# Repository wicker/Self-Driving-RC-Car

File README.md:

Self-Driving-RC-Car
===================

Testing out Kalman filter and SLAM code on a vehicle which can't fall out of the sky.

Hardware
--------

IMX (Imex) Firefox 1/10 scale RC car contains one RC550 brushed hobby DC motor and one three-wire RadioShack hobby servo. 

v1 controller is an Arduino Uno with VNH5019 Dual Motor Driver Carrier Shield from Pololu. 

v2 controller is an STM32F4-Discovery board with VNH5019 Dual Motor Driver Carrier shield from Pololu.

v3 controller is a custom Foxcar Control Board v1.

v4 controller is a custom Foxcar Control Board v2.

Software
--------

**v1 - Arduino**

A simple Arduino sketch to drive the motor in forward and reverse while turning the servo to steer the vehicle. Libraries used:

- [Zambetti's ASCIITable](http://arduino.cc/en/Tutorial/ASCIITable)
- [SoftwareSerial](http://arduino.cc/en/Reference/SoftwareSerial)
- [mem's ServoTimer2](http://forum.arduino.cc/index.php/topic,21975.0.html)
- [Pololu's VNH5019 Motor Driver Shield](https://github.com/pololu/dual-vnh5019-motor-shield)

**v2 - STM32F4-Discovery**

Putting everything together. 

- [Pololu's VNH5019 Motor Driver Shield](https://github.com/pololu/dual-vnh5019-motor-shield)

License
-------

Released under the 3-clause BSD. http://opensource.org/licenses/BSD-3-Clause

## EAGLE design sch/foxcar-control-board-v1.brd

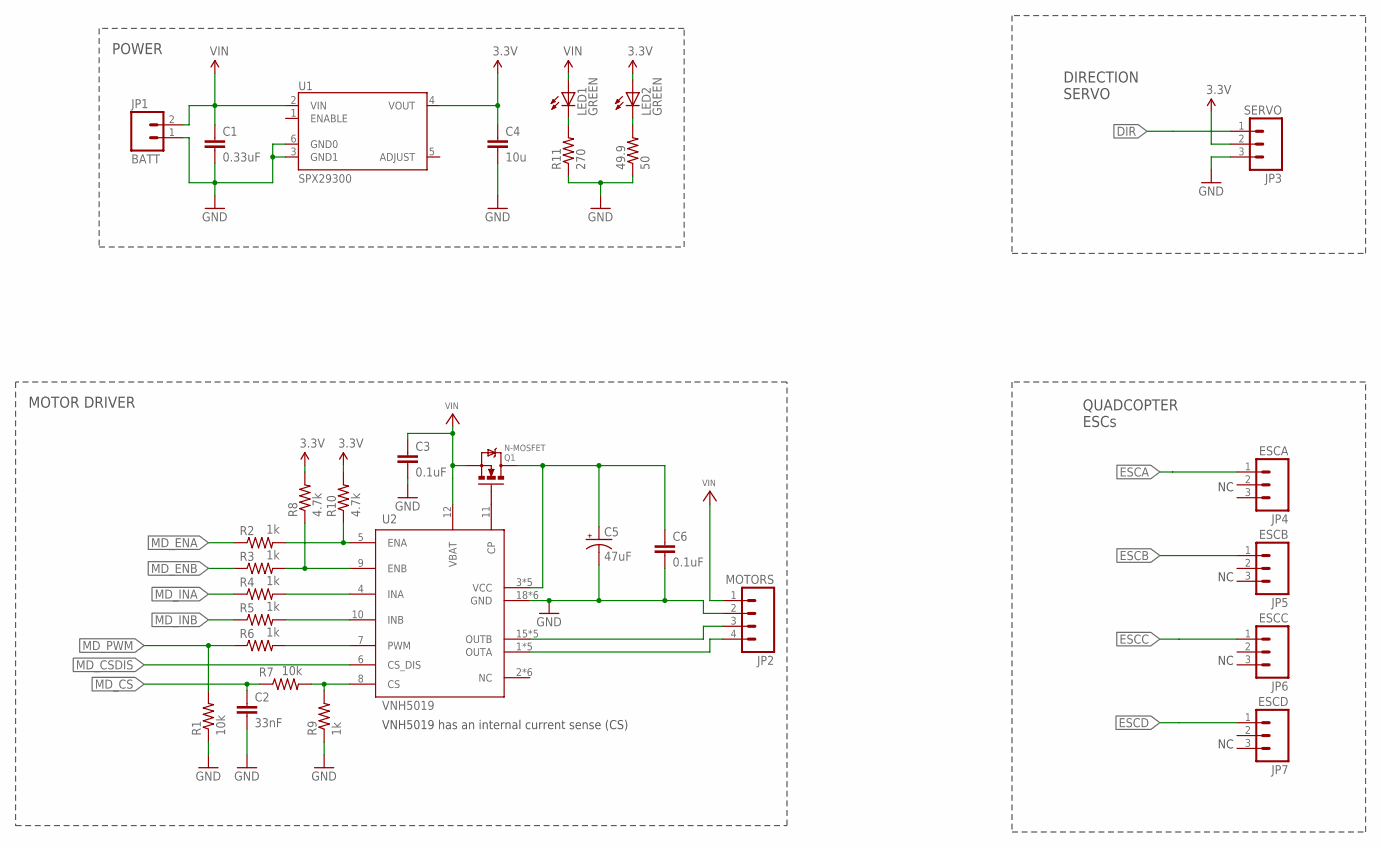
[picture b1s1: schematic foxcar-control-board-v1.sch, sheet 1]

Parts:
49.9: 50; 0402-RES
C1: 0.33uF; 0402-CAP
C2: 33nF; 0402-CAP
C3, C6: 0.1uF; 0402-CAP
C4: 10u; 0603-CAP
C5: 47uF; PANASONIC_D
JP1: BATT; SCREWTERMINAL-3.5MM-2_LOCK
JP2: MOTORS; SCREWTERMINAL-3.5MM-4_LOCK
JP3: SERVO; 1X03_LOCK_LONGPADS
JP4: ESCA; 1X03_LOCK_LONGPADS
JP5: ESCB; 1X03_LOCK_LONGPADS
JP6: ESCC; 1X03_LOCK_LONGPADS
JP7: ESCD; 1X03_LOCK_LONGPADS
LED1, LED2: GREEN; CHIPLED_0603
Q1: N-MOSFET; TO220V
R1: 10k; 0603-RES
R2, R3, R4, R5, R6, R9: 1k; 0402-RES
R7: 10k; 0402-RES
R8, R10: 4.7k; 0402-RES
R11: 270; 0603-RES
U1: SPX29300; TO263-5
U2: VNH5019; MULTIPOWERSO-30

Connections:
3.3V: C4.1, JP3.2, LED2.A, R8.2, R10.2, U1.4 (VOUT); also elsewhere on the board
CP: Q1.1 (G), U2.11 (CP)
CS: R7.2, R9.2, U2.8 (CS)
DIR: JP3.1; also elsewhere on the board
ENA: R2.2, R10.1, U2.5 (ENA)
ENB: R3.2, R8.1, U2.9 (ENB)
ESCA: JP4.1; also elsewhere on the board
ESCB: JP5.1; also elsewhere on the board
ESCC: JP6.1; also elsewhere on the board
ESCD: JP7.1; also elsewhere on the board
GND: 49.9.1, C1.2, C2.2, C3.2, C4.2, C5.-, C6.2, JP1.1, JP2.2, JP3.3, R1.1, R9.1, R11.1, U1.3 (GND1), U1.6 (GND0), U2.18 (GND), U2.19 (GND), U2.20 (GND), U2.26 (GND), U2.27 (GND), U2.28 (GND); also elsewhere on the board
INA: R4.2, U2.4 (INA)
INB: R5.2, U2.10 (INB)
MD_CS: C2.1, R7.1; also elsewhere on the board
MD_CSDIS: U2.6 (CS_DIS); also elsewhere on the board
MD_ENA: R2.1; also elsewhere on the board
MD_ENB: R3.1; also elsewhere on the board
MD_INA: R4.1; also elsewhere on the board
MD_INB: R5.1; also elsewhere on the board
MD_PWM: R1.2, R6.1; also elsewhere on the board
unnamed: 49.9.2, LED2.C
unnamed: LED1.C, R11.2
OUTA: JP2.4, U2.1 (OUTA), U2.25 (OUTA), U2.30 (OUTA), U2.OUTA, U2.OUTA@1 (OUTA)
OUTB: JP2.3, U2.15 (OUTB), U2.16 (OUTB), U2.21 (OUTB), U2.OUTB, U2.OUTB@1 (OUTB)
PWM: R6.2, U2.7 (PWM)
VCC: C5.+, C6.1, Q1.2 (D), U2.3 (VCC), U2.13 (VCC), U2.23 (VCC), U2.VCC, U2.VCC@1 (VCC)
VIN: C1.1, C3.1, JP1.2, JP2.1, LED1.A, Q1.3 (S), U1.2 (VIN), U2.12 (VBAT); also elsewhere on the board

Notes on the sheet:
VNH5019 has an internal current sense (CS)
POWER
MOTOR DRIVER
DIRECTION SERVO
QUADCOPTER ESCs

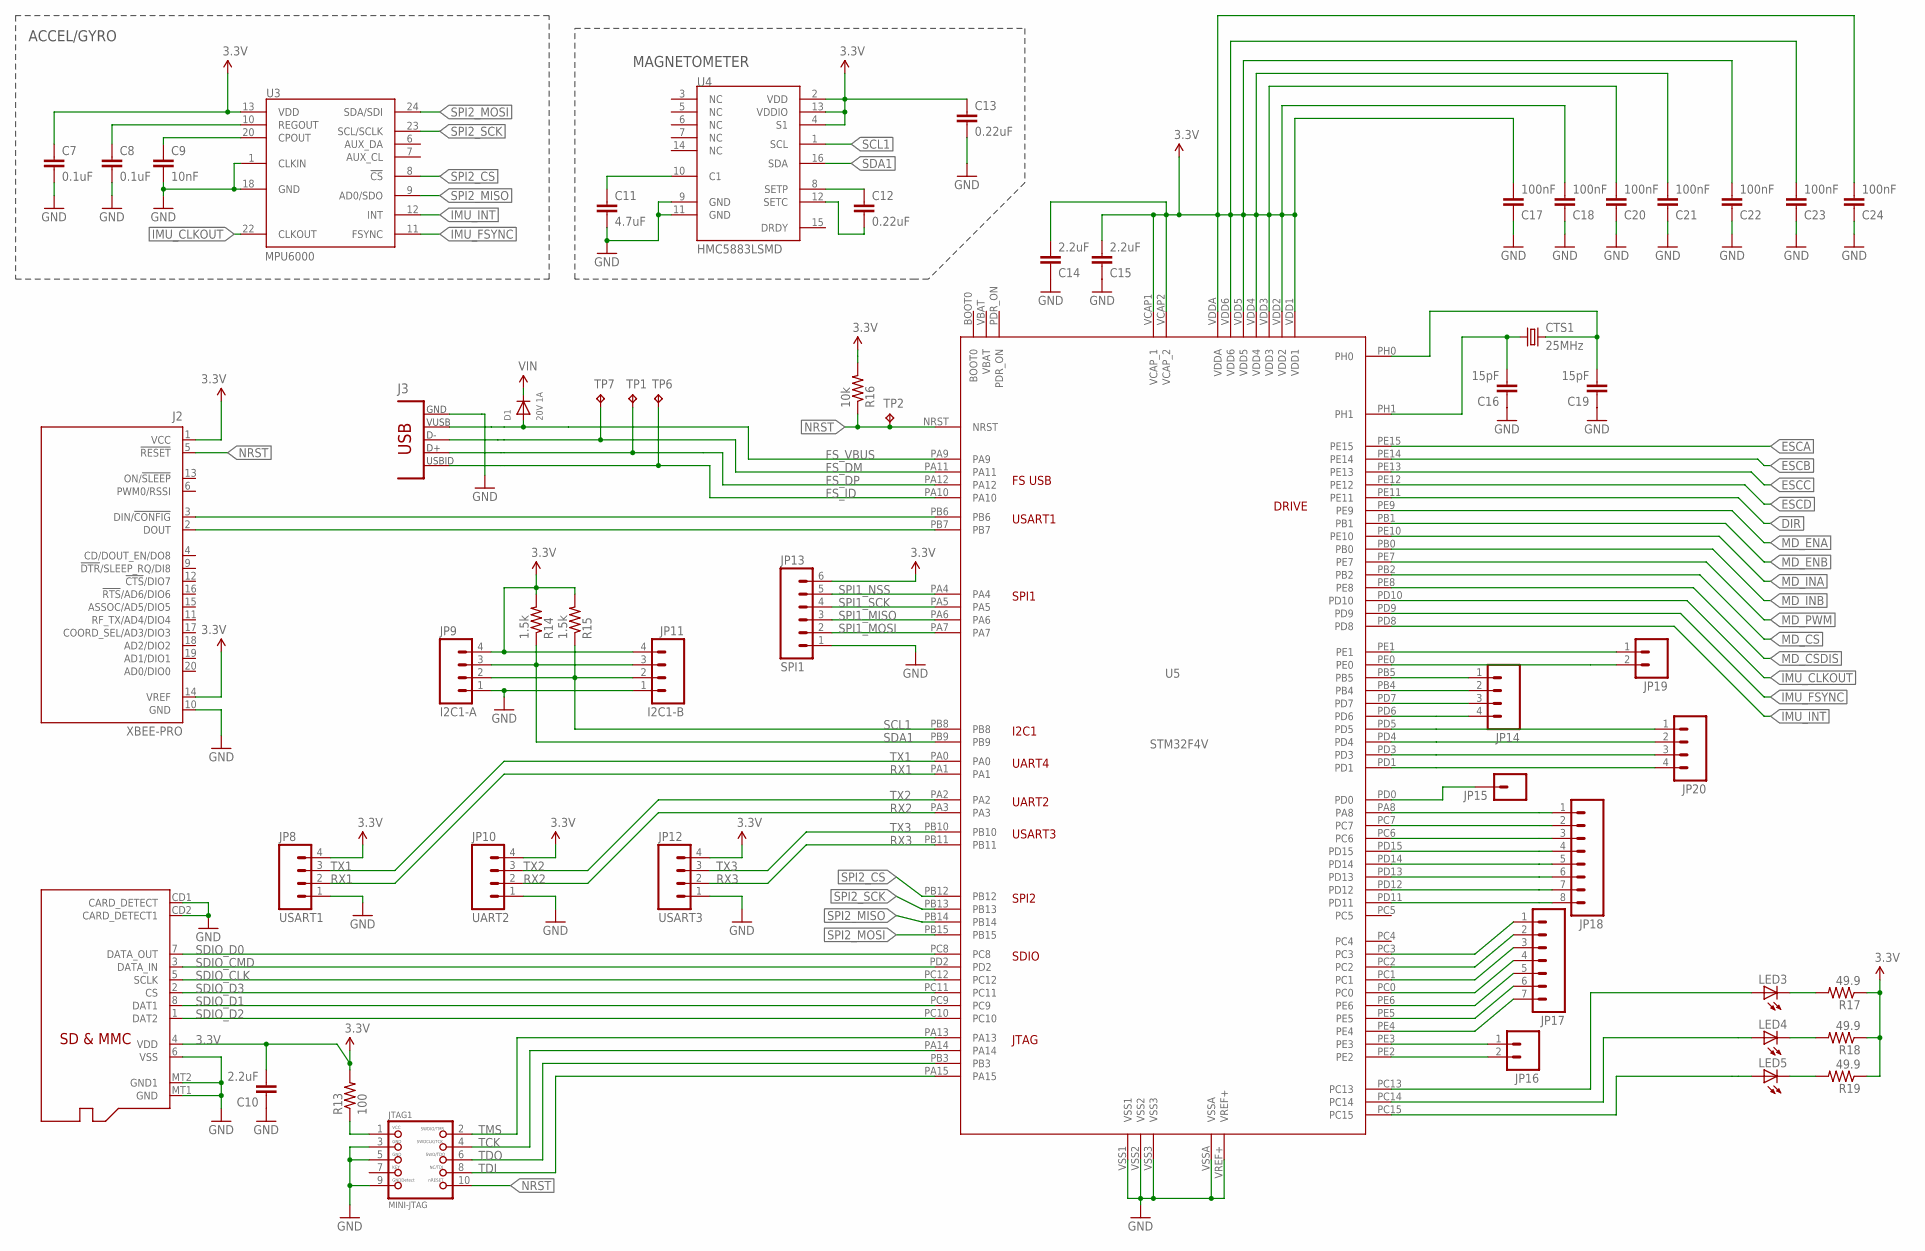
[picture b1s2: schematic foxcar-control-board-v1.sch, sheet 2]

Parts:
C7, C8: 0.1uF; 0402-CAP
C9: 10nF; 0402-CAP
C10, C14, C15: 2.2uF; 0402-CAP
C11: 4.7uF; 0402-CAP
C12, C13: 0.22uF; 0402-CAP
C16, C19: 15pF; 0402-CAP
C17, C18, C20, C21, C22, C23, C24: 100nF; 0402-CAP
CTS1: 25MHz; CTS406
D1: 20V 1A; SMADIODE
J1: MICROSD
J2: XBEE-PRO
J3: CON-USB-F-MICRO-B; CONN_USB_MICRO-B
JP8: USART1; 1X04_LOCK_LONGPADS
JP9: I2C1-A; 1X04_LOCK_LONGPADS
JP10: UART2; 1X04_LOCK_LONGPADS
JP11: I2C1-B; 1X04_LOCK_LONGPADS
JP12: USART3; 1X04_LOCK_LONGPADS
JP13: SPI1; 1X06_LOCK_LONGPADS
JP14, JP20: M04LOCK; 1X04_LOCK
JP15: M01PTH; 1X01
JP16: M02LOCK_LONGPADS; 1X02_LOCK_LONGPADS
JP17: M07LOCK; 1X07_LOCK
JP18: M08LOCK_LONGPADS; 1X08_LOCK_LONGPADS
JP19: M02LOCK; 1X02_LOCK
JTAG1: MINI-JTAG; 2X05_1.27MM_SMT
LED3, LED4, LED5: LEDCHIPLED_0603; CHIPLED_0603
R13: 100; 0402-RES
R14, R15: 1.5k; 0402-RES
R16: 10k; 0402-RES
R17, R18, R19: 49.9; 0402-RES
TP1, TP2, TP6, TP7: TPTP06R; TP06R
U3: MPU6000; QFN.24.4X4
U4: HMC5883LSMD; 16LPCC
U5: STM32F4V; LQFP100

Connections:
3.3V: C7.1, C10.2, C13.1, C14.2, C15.2, C17.2, C18.2, C20.2, C21.2, C22.2, C23.2, C24.2, J1.4 (VDD), J2.1 (VCC), J2.14 (VREF), JP8.4, JP9.4, JP10.4, JP11.4, JP12.4, JP13.6, R13.2, R14.2, R15.2, R16.2, R17.1, R18.1, R19.1, U3.13 (VDD), U4.2 (VDD), U4.4 (S1), U4.13 (VDDIO), U5.VCAP1 (VCAP_1), U5.VCAP2 (VCAP_2), U5.VDD1, U5.VDD2, U5.VDD3, U5.VDD4, U5.VDD5, U5.VDD6, U5.VDDA; also elsewhere on the board
DIR: U5.PE11; also elsewhere on the board
ESCA: U5.PE15; also elsewhere on the board
ESCB: U5.PE14; also elsewhere on the board
ESCC: U5.PE13; also elsewhere on the board
ESCD: U5.PE12; also elsewhere on the board
FS_DM: J3.P2 (D-), TP7.TP, U5.PA11
FS_DP: J3.P3 (D+), TP1.TP, U5.PA12
FS_ID: J3.P4 (USBID), TP6.TP, U5.PA10
FS_VBUS: D1.A, J3.P1 (VUSB), U5.PA9
GND: C7.2, C8.2, C9.2, C10.1, C11.2, C13.2, C14.1, C15.1, C16.1, C17.1, C18.1, C19.1, C20.1, C21.1, C22.1, C23.1, C24.1, J1.6 (VSS), J1.CD1 (CARD_DETECT), J1.CD2 (CARD_DETECT1), J1.MT1 (GND), J1.MT2 (GND1), J2.10 (GND), J3.P5 (GND), JP8.1, JP9.1, JP10.1, JP11.1, JP12.1, JP13.1, JTAG1.3, JTAG1.5, JTAG1.9, U3.1 (CLKIN), U3.18 (GND), U4.9 (GND), U4.11 (GND), U5.VREF+, U5.VSS1, U5.VSS2, U5.VSS3, U5.VSSA; also elsewhere on the board
IMU_CLKOUT: U3.22 (CLKOUT), U5.PD10
IMU_FSYNC: U3.11 (FSYNC), U5.PD9
IMU_INT: U3.12 (INT), U5.PD8
LED_B: LED5.A, U5.PC15
LED_G: LED4.A, U5.PC14
LED_R: LED3.A, U5.PC13
MD_CS: U5.PB2; also elsewhere on the board
MD_CSDIS: U5.PE8; also elsewhere on the board
MD_ENA: U5.PE9; also elsewhere on the board
MD_ENB: U5.PB1; also elsewhere on the board
MD_INA: U5.PE10; also elsewhere on the board
MD_INB: U5.PB0; also elsewhere on the board
MD_PWM: U5.PE7; also elsewhere on the board
unnamed: JP18.1, U5.PA8
unnamed: C12.2, U4.12 (SETC)
unnamed: LED3.C, R17.2
unnamed: LED4.C, R18.2
unnamed: LED5.C, R19.2
unnamed: JP17.4, U5.PC0
unnamed: JP17.3, U5.PC1
unnamed: C12.1, U4.8 (SETP)
unnamed: C11.1, U4.10 (C1)
unnamed: JP17.2, U5.PC2
unnamed: JP19.1, U5.PE1
unnamed: JP17.1, U5.PC3
unnamed: C9.1, U3.20 (CPOUT)
unnamed: JTAG1.1, R13.1
unnamed: JP16.2, U5.PE2
unnamed: JP16.1, U5.PE3
unnamed: JP17.7, U5.PE4
unnamed: JP17.6, U5.PE5
unnamed: JP17.5, U5.PE6
unnamed: JP18.2, U5.PC7
unnamed: JP18.3, U5.PC6
unnamed: JP18.4, U5.PD15
unnamed: JP18.5, U5.PD14
unnamed: JP18.6, U5.PD13
unnamed: JP18.7, U5.PD12
unnamed: JP18.8, U5.PD11
unnamed: JP19.2, U5.PE0
unnamed: JP14.1, U5.PB5
unnamed: JP14.2, U5.PB4
unnamed: JP14.3, U5.PD7
unnamed: JP14.4, U5.PD6
unnamed: JP20.1, U5.PD5
unnamed: JP20.2, U5.PD4
unnamed: JP20.3, U5.PD3
unnamed: JP20.4, U5.PD1
unnamed: JP15.1, U5.PD0
NRST: J2.5 (!RESET), JTAG1.10, R16.1, TP2.TP, U5.NRST
OSC_IN1: C19.2, CTS1.3 (2), U5.PH0
OSC_OUT1: C16.2, CTS1.1, U5.PH1
REGOUT: C8.1, U3.10 (REGOUT)
RX1: JP8.2, U5.PA1
RX2: JP10.2, U5.PA3
RX3: JP12.2, U5.PB11
RX_DOUT1: J2.2 (DOUT), U5.PB7
SCL1: JP9.2, JP11.2, R15.1, U4.1 (SCL), U5.PB8
SDA1: JP9.3, JP11.3, R14.1, U4.16 (SDA), U5.PB9
SDIO_CLK: J1.5 (SCLK), U5.PC12
SDIO_CMD: J1.3 (DATA_IN), U5.PD2
SDIO_D0: J1.7 (DATA_OUT), U5.PC8
SDIO_D1: J1.8 (DAT1), U5.PC9
SDIO_D2: J1.1 (DAT2), U5.PC10
SDIO_D3: J1.2 (CS), U5.PC11
SPI1_MISO: JP13.3, U5.PA6
SPI1_MOSI: JP13.2, U5.PA7
SPI1_NSS: JP13.5, U5.PA4
SPI1_SCK: JP13.4, U5.PA5
SPI2_CS: U3.8 (!CS), U5.PB12
SPI2_MISO: U3.9 (AD0/SDO), U5.PB14
SPI2_MOSI: U3.24 (SDA/SDI), U5.PB15
SPI2_SCK: U3.23 (SCL/SCLK), U5.PB13
TCK: JTAG1.4, U5.PA14
TDI: JTAG1.8, U5.PA15
TDO: JTAG1.6, U5.PB3
TMS: JTAG1.2, U5.PA13
TX1: JP8.3, U5.PA0
TX2: JP10.3, U5.PA2
TX3: JP12.3, U5.PB10
TX_DIN1: J2.3 (DIN/!CONFIG), U5.PB6
VIN: D1.C; also elsewhere on the board

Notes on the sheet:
ACCEL/GYRO
MAGNETOMETER

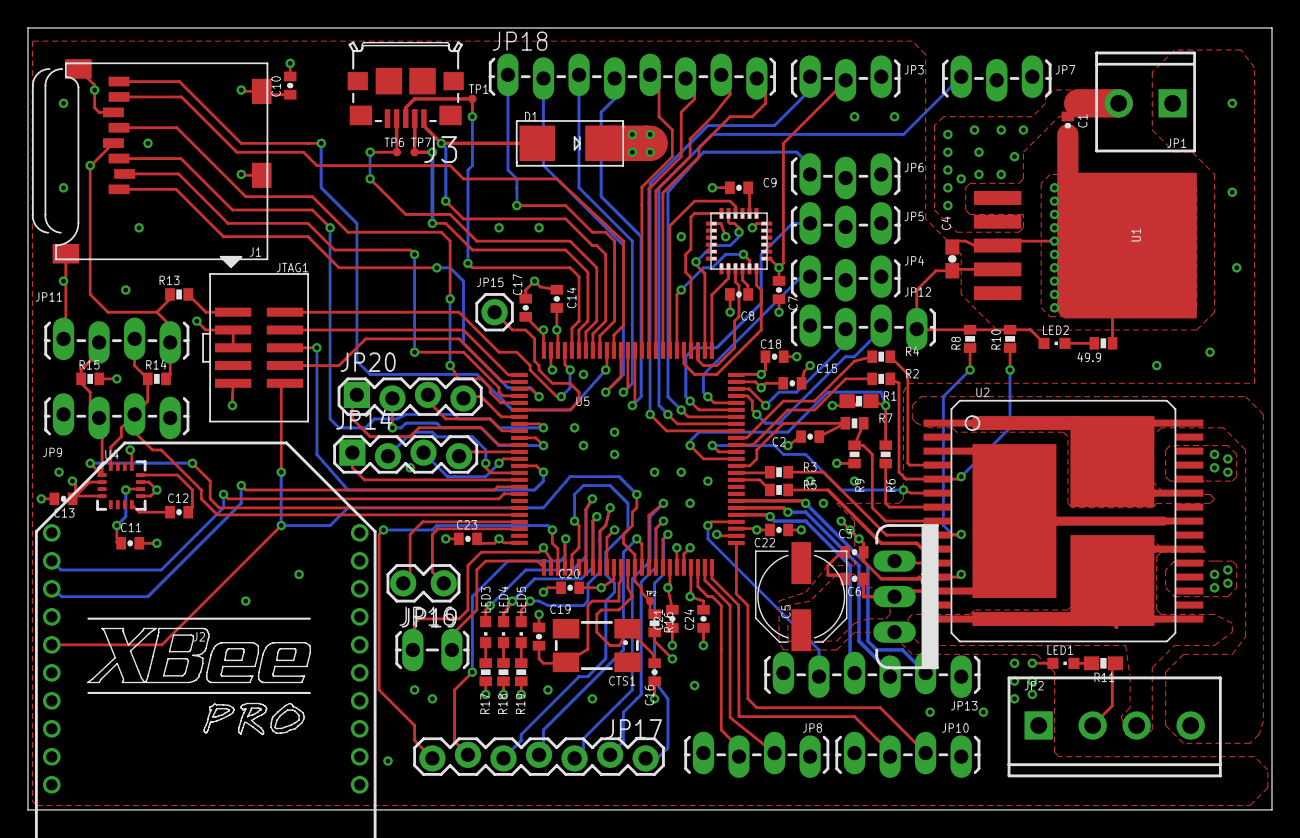
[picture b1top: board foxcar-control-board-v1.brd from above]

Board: 4 copper layers, 88.9 x 55.9 mm, 84 parts (0 on the bottom side), 105 nets.

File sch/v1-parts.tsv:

Parts	Qty	Name	Manufacturer	Part Number	Package
C1	1	Cap, Ceramic, 0.33uF, 25V, 10%	TDK	C1005X5R1E334K050BB	0402
C2	1	Cap, Ceramic, 33nF, 16V, 10%	SMTZone	SMT KIT	0402
"C3,C6-C8,C17,
C18,C20-C24"	11	Cap, Ceramic, 0.1uF, 10V, 10%	SMTZone	SMT KIT	0402
C4	1	Cap, Ceramic, 10uF, 10V, 10%	Samsung	CL05A106MP5NUNC	0402
C5	1	Cap, Aluminum, 47uF, 25V, 10%	Panasonic	EEE-1EA470WP	RADCAN
C9	1	Cap, Ceramic, 10nF, 50V, 10%	SMTZone	SMT KIT	0402
C10,C14,C15	3	Cap, Ceramic, 2.2uF, 10V, 20%	Kemet	C0402C225M8PACTU	0402
C11	1	Cap, Ceramic, 4.7uF, 10V, 20%	Samsung	CL05A475MP5NRNC	0402
C12,C13	2	Cap, Ceramic, 0.22uF, 6.3V, 10%	SMTZone	SMT KIT	0402
C16,C19	1	Cap, Ceramic, 15pF, 50V, 5%	SMTZone	SMT KIT	0402
CTS1	1	Crystal, 25MHz, 18pF	CTS	406I35D25M00000	CTS406
D1	1	Diode, 20V, 1A	Diodes Inc	B120-13-F	SMA
J1	1	Conn, microSD, Push-Push	3M	2908-05WB-MG	microSD
J2	1	Header, XBee Pro	Sparkfun	PRT-08272 	Header
J3	1	Conn, Micro-USB B, SMD	TE Connectivity	1981568-1	microUSB-B
JP1	1	Term Block, 2pin, R/A, 5mm	On Shore	OSTTH020160	Header
JP2	1	Term Block, 4pin, R/A, 5mm	On Shore	OSTTH040160	Header
JP3-JP7	5	Header, 1x3	--	On Hand	
JP8-JP12	Lots	Headers, 0.1in	--	On Hand	
LED1-5	5	LED, Green, 568nm	Kingbright	APT1608SGC	0603
Q1	1	MOSFET, NPN, 30V, 80A	Infineon	IPP034NE7N3 G	TO-220-3
R1,R7,R16	3	Resistor, 10k, 1%, 1/10W	SMTZone	SMT KIT	0402
R2-R6,R9	6	Resistor, 1k, 1%, 1/10W	SMTZone	SMT KIT	0402
R8,R10	2	Resistor, 4.7k, 1%, 1/10W	SMTZone	SMT KIT	0402
R11	1	Resistor, 270, 5%, 1/4W	Rohm	ESR03EZPJ271	0603
R12,R17-R19	4	Resistor, 49.9, 1%, 1/10W	SMTZone	SMT KIT	0402
R13	1	Resistor, 100, 1%, 1/10W	SMTZone	SMT KIT	0402
R14-R15	2	Resistor 1.5k, 1%, 1/10W	SMTZone	SMT KIT	0402
U1	1	IC, Volt Reg, LDO, 3.3V, 3A	STMicroelectronics	SPX29300	TO263-5
U2	1	IC, Motor Driver	STMicroelectronics	VNH5019	MULTIPOWERSO-30
U3	1	IC, Gyro/Accel, 6-Axis, SPI	InvenSense	MPU6000	24QFN
U4	1	IC, Compass, 3-Axis, I2C	Honeywell	HMC5883L	16LPCC
U5	1	IC, MCU, 32bit, 1MB Flash	STMicroelectronics	STM32F407VGT6	LQFP100

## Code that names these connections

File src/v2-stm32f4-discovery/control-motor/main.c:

// Servo control
//
// Servo on pin PB8 uses TIM4 channel 3 on alternate function 2
// TIM4 supports PWM driving.
// PWMD4 is a HAL-defined driver associated with TIM4.
 
#include "ch.h"
#include "hal.h"
 
#define LEFT 0
#define RIGHT 1

#define INAPIN 1 // PB1
#define INBPIN 2 // PB2
 
static PWMConfig pwmcfg = {
  1000000, // 1MHz PWM clock
  20000, // PWM period 20ms 
  NULL, // No callback 
  {
    {PWM_OUTPUT_DISABLED, NULL},      
    {PWM_OUTPUT_DISABLED, NULL},     
    {PWM_OUTPUT_ACTIVE_HIGH, NULL},   
    {PWM_OUTPUT_DISABLED, NULL},       
  },
  0
};
 
int main(void)
{
  halInit();
  chSysInit();
  
  palSetPadMode(GPIOB, 0, PAL_MODE_ALTERNATE(2)); // alt mode is PWM-enabled TIM3
  palSetPadMode(GPIOB, INAPIN, PAL_MODE_OUTPUT_PUSHPULL); // set INA to be an output
  palSetPadMode(GPIOB, INBPIN, PAL_MODE_OUTPUT_PUSHPULL); // set INB to be an output
   
  pwmStart(&PWMD3, &pwmcfg); // TIM3 for motors
 
  while (TRUE) {
    // one direction (possibly forward)
    pwmEnableChannel(&PWMD3, 3, 500);
    palSetPad(GPIOB, INAPIN);
    palClearPad(GPIOB, INBPIN);
    chThdSleepMilliseconds(3000);

    // the other direction (possibly backward)
    pwmEnableChannel(&PWMD3, 3, 500);
    palSetPad(GPIOB, INBPIN);
    palClearPad(GPIOB, INAPIN);
    chThdSleepMilliseconds(3000);
  }
}

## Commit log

2012-10-09 Basic outline of a basic Kalman filter.
2012-10-21 Potential structure for source code.
2012-10-21 Remove main.h
2012-10-21 Figuring out structure.
2012-10-21 Consolidating matrix math files.
2012-10-21 Testing if this compiles.
2012-10-21 File takes command line inputs of filter type and value of T.
2012-10-22 Transpose function works. Might have the hang of this multidimensional array thing.
2012-10-22 Removed matrix math functions to their own file.
2012-10-23 Added KF functions. Updated matrix math files. This is all structural. All algorithm stuff needs work.
2012-10-23 Added inverse() function.
2012-10-23 Assigned initial values to matrices. Basic algorithm in place.
2012-11-10 Change matrix form to struct with dims and data. Use_kf() now uses those forms.
2012-11-13 Half the algo written. Lacking in functions.
2012-11-15 Filter finished. All math is includedin filter/use_kf.c. Needs to be pulled out into matrix header.
2012-11-15 Remove file.
2012-11-15 Added run script.
2012-11-16 Program now takes T and duration as command line argument.
2013-11-11 Modded an RC car. Motor and servo control test complete.
2013-11-11 Added libraries.
2013-11-11 Formatting of links.
2013-11-11 Formatting.
2013-11-23 Pubs and start of a schematic.
2013-11-24 Clean-up.
2013-11-24 Ignore intermittent Eagle saves.
2013-11-24 Power and voltage regs done. Started current sense.
2013-11-25 Added IMU sensors (gyro, accel, compass) using Sparkfun references.
2013-11-28 Added custom STM32F4 64-pin symbol and device to layout.
2013-11-28 Added most of sheet 3 stm32f4 with all its connections.
2013-11-28 Tested the Maxbotix EZ4, then added it to sheet 3. Wires in place, still need Rs and Cs.
2013-12-09 Schematic done! Passes ERC.
2013-12-10 Info added. Small cleanups.
2013-12-10 The last of the ERCs. Chose diode and LEDs.
2013-12-10 Set up Eagle board with Sparkfun 4-layer DRU. Set up layers. Started with power section.
2013-12-13 Almost done with power layout. Minor stm32 symbol changes.
2013-12-14 Making progress on layout.
2013-12-15 Going to set aside that layout and try a fresh start.
2013-12-15 Trying a new technique: placing all components around the stm32f4 with relatively direct paths, then seeing how badly I can fuck it up.
2013-12-15 Making much better progress on stm32. relocating to house because I live in a land of less-than-24-hour coffee shops. :(
2013-12-15 Everything laid out except for the power stuff.
2013-12-15 Layout done, screenshots uploaded, parts list added.
2013-12-20 Added library for this repo.
2013-12-21 Added exported library to sch directory.
2013-12-21 Made filename smaller so Github can display it.
2013-12-22 Made BOM and had to make some changes. Final parts list included.
2013-12-22 Making TSV file all prettified.
2013-12-30 Added a couple of basic serial tests from Ladyada and Arduino.
2013-12-30 Fixes.
2013-12-30 Remote control of on-car servo via XBees from minicom.
2013-12-30 Added .swp file type.
2014-03-28 Split code into versions with better folders.
2014-03-28 Ready for control board build.
2014-03-28 Added basic blinkled example to prove toolchain works.
2014-03-28 Figuring out what to actually put in the repo.
2014-03-28 Pardon the excessive pushing. But aren't we used to that by now?
2014-03-28 Ignoring build folder in stm32 projects.
2014-03-28 Ignoring .dep folder in stm32 projects.
2014-03-28 Updated README with versions.
2014-03-29 Added PWM-driven LED and PWM-driven servo to stm32f4.
2014-03-29 Removed file.
2014-03-29 Testing servo and motor control code.
2014-04-20 Added ChibiOS submodule.
2014-04-20 Verified this code works with Arduino, VNH5019, and STM32F4 running onboard car.

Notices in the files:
parts and their libraries:
SparkFun-Connectors: Licensing: CC v3.0 Share-Alike You are welcome to use this library for commercial purposes.
